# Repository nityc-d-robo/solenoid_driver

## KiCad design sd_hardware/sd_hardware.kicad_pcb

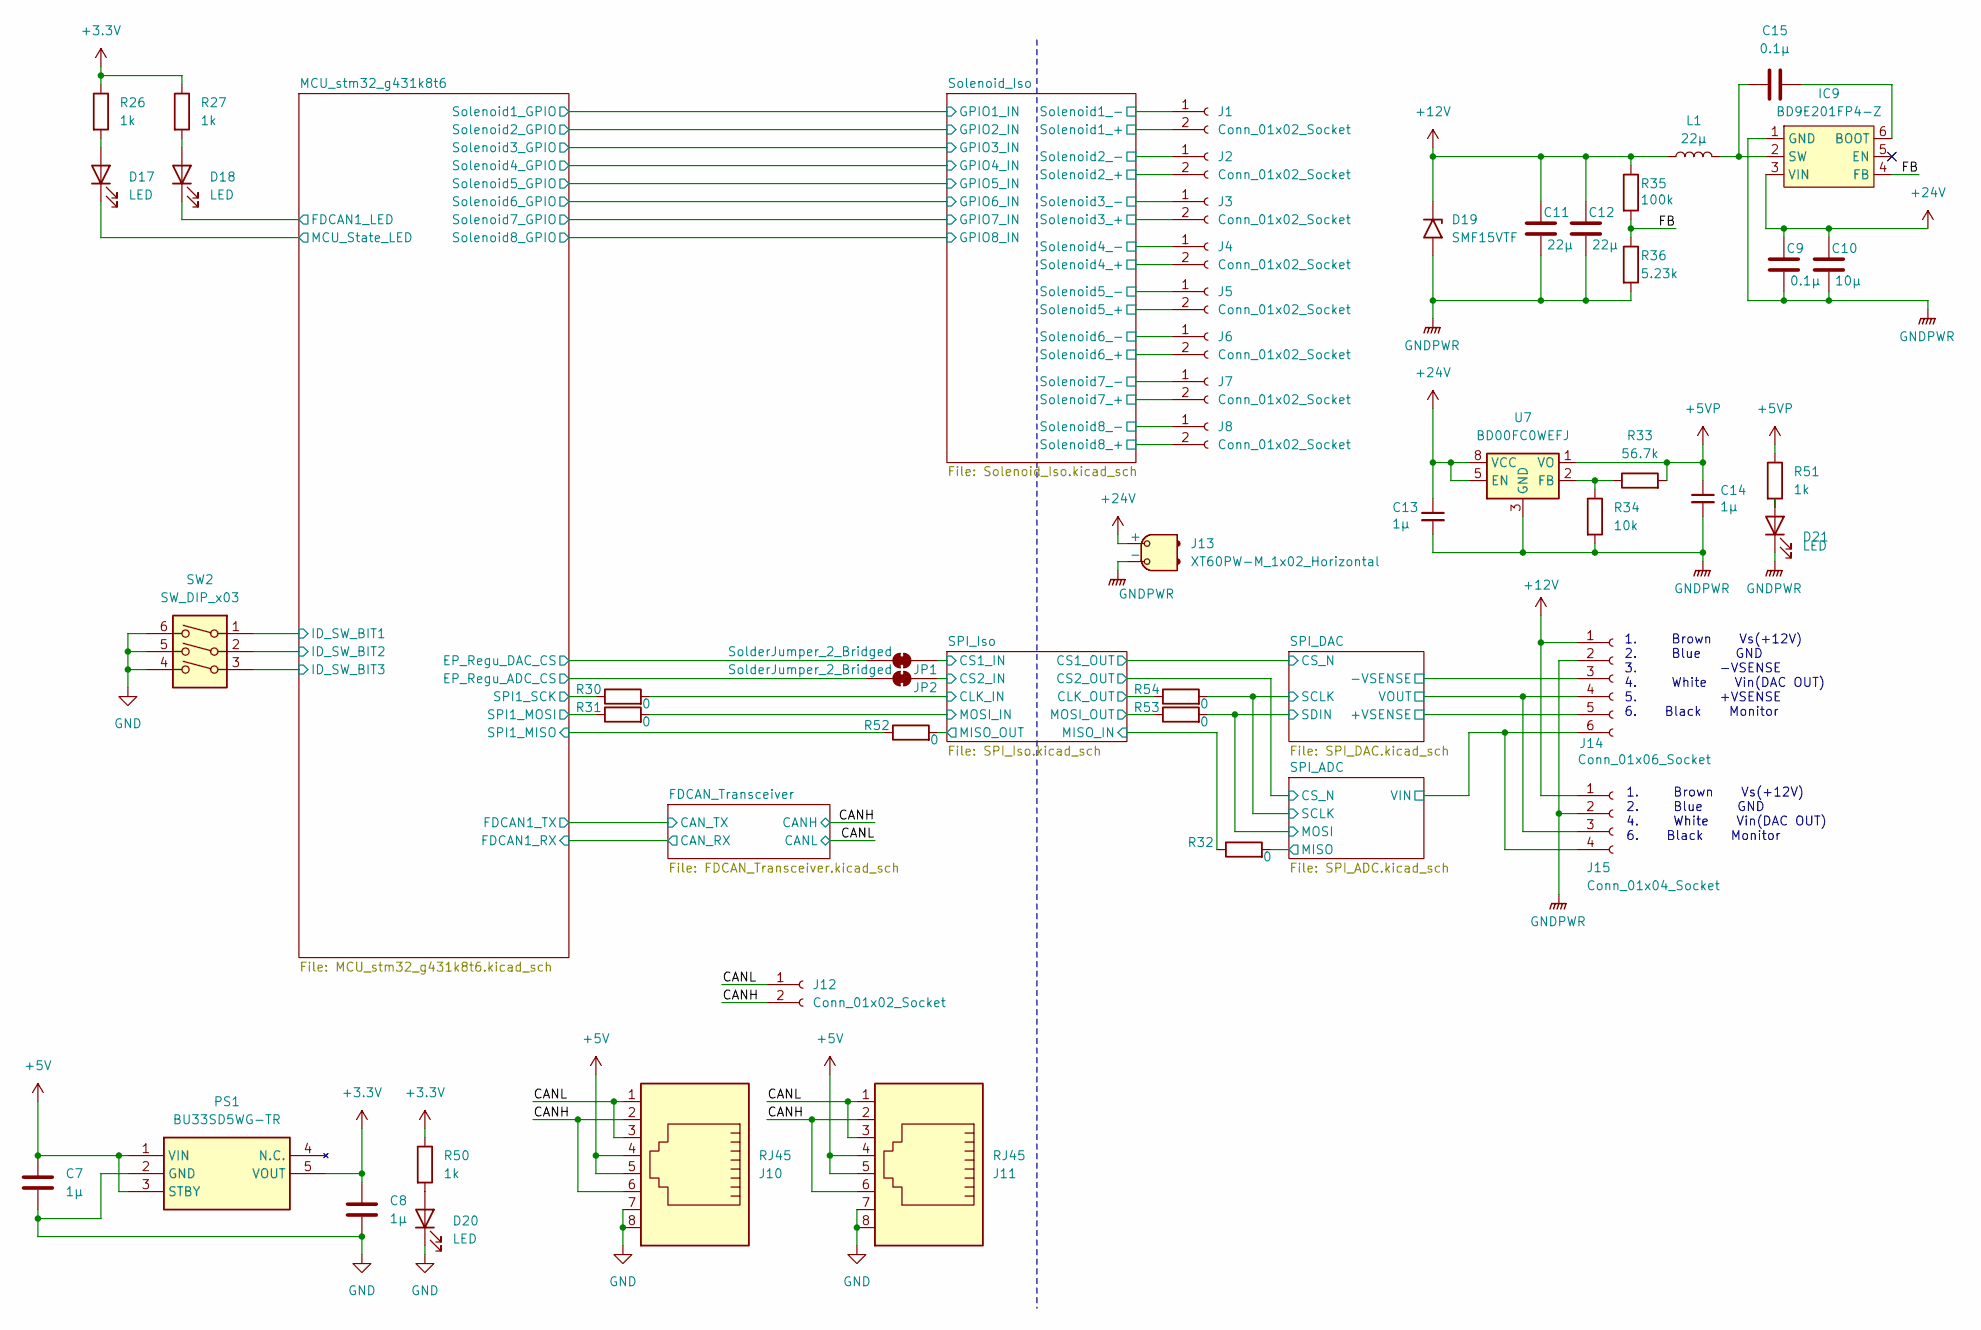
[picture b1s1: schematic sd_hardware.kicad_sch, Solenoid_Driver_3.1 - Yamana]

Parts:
C7, C8, C13, C14: 1μ; C_0603_1608Metric_Pad1.08x0.95mm_HandSolder
C9, C15: 0.1μ; C_0603_1608Metric_Pad1.08x0.95mm_HandSolder
C10: 10μ; C_0603_1608Metric_Pad1.08x0.95mm_HandSolder
C11, C12: 22μ; C_1210_3225Metric_Pad1.33x2.70mm_HandSolder
D17, D18, D20, D21: LED; LED_0603_1608Metric_Pad1.05x0.95mm_HandSolder
D19: SMF15VTF; D_SOD-123F
IC9: BD9E201FP4-Z; TSOT-23-6
J1, J2, J3, J4, J5, J6, J7, J8, J12: Conn_01x02_Socket; JST_XH_B2B-XH-A_1x02_P2.50mm_Vertical
J10, J11: RJ45; RJ45_Amphenol_54602-x08_Horizontal
J13: XT60PW-M_1x02_Horizontal; AMASS_XT60PW-M_1x02_P7.20mm_Horizontal
J14: Conn_01x06_Socket; JST_XH_B6B-XH-A_1x06_P2.50mm_Vertical
J15: Conn_01x04_Socket; JST_XH_B4B-XH-A_1x04_P2.50mm_Vertical
JP1, JP2: SolderJumper_2_Bridged; SolderJumper-2_P1.3mm_Bridged2Bar_RoundedPad1.0x1.5mm
L1: 22μ; RP1315BNP-220M
PS1: BU33SD5WG-TR; SOT95P280X125-5N; Mouser Part Number 755-BU33SD5WG-TR
R26, R27, R50, R51: 1k; R_0603_1608Metric_Pad0.98x0.95mm_HandSolder
R30, R31, R32, R52, R53, R54: 0; R_0603_1608Metric_Pad0.98x0.95mm_HandSolder
R33: 56.7k; R_0603_1608Metric_Pad0.98x0.95mm_HandSolder
R34: 10k; R_0603_1608Metric_Pad0.98x0.95mm_HandSolder
R35: 100k; R_0603_1608Metric_Pad0.98x0.95mm_HandSolder
R36: 5.23k; R_0603_1608Metric_Pad0.98x0.95mm_HandSolder
SW2: SW_DIP_x03; DS04-254-2-03BK-SMT
U7: BD00FC0WEFJ; HTSOP-8-1EP_3.9x4.9mm_P1.27mm_EP2.4x3.2mm

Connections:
+3.3V: C8.1, PS1.5 (VOUT), R26.1, R27.1, R50.1; also elsewhere on the board
+5V: C7.1, J10.4, J10.5, J11.4, J11.5, PS1.1 (VIN), PS1.3 (STBY); also elsewhere on the board
+5VP: C14.1, R33.2, R51.1, U7.1 (VO); also elsewhere on the board
+12V: C11.1, C12.1, D19.1 (A1), J1.2, J2.2, J3.2, J4.2, J5.2, J6.2, J7.2, J8.2, J14.1, J15.1, L1.1, R35.1; also elsewhere on the board
+24V: C9.1, C10.1, C13.1, IC9.3 (VIN), J13.2 (+), U7.5 (EN), U7.8 (VCC)
/CANH: J10.2, J10.6, J11.2, J11.6, J12.2; also elsewhere on the board
/CANL: J10.1, J10.3, J11.1, J11.3, J12.1; also elsewhere on the board
/FB: IC9.4 (FB), R35.2, R36.1
/MCU_stm32_g431k8t6/EP_Regu_ADC_CS: JP2.1 (A); also elsewhere on the board
/MCU_stm32_g431k8t6/EP_Regu_DAC_CS: JP1.1 (A); also elsewhere on the board
/MCU_stm32_g431k8t6/FDCAN1_LED: D18.1 (K); also elsewhere on the board
/MCU_stm32_g431k8t6/ID_SW_BIT1: SW2.1; also elsewhere on the board
/MCU_stm32_g431k8t6/ID_SW_BIT2: SW2.2; also elsewhere on the board
/MCU_stm32_g431k8t6/ID_SW_BIT3: SW2.3; also elsewhere on the board
/MCU_stm32_g431k8t6/MCU_State_LED: D17.1 (K); also elsewhere on the board
/MCU_stm32_g431k8t6/SPI1_MISO: R52.1; also elsewhere on the board
/MCU_stm32_g431k8t6/SPI1_MOSI: R31.1; also elsewhere on the board
/MCU_stm32_g431k8t6/SPI1_SCK: R30.1; also elsewhere on the board
/SPI_ADC/MISO: R32.2; also elsewhere on the board
/SPI_ADC/MOSI: R53.2; also elsewhere on the board
/SPI_ADC/SCLK: R54.2; also elsewhere on the board
/SPI_ADC/VIN: J14.6, J15.4; also elsewhere on the board
/SPI_DAC/+VSENSE: J14.5; also elsewhere on the board
/SPI_DAC/-VSENSE: J14.3; also elsewhere on the board
/SPI_DAC/VOUT: J14.4, J15.3; also elsewhere on the board
/SPI_Iso/CLK_IN: R30.2; also elsewhere on the board
/SPI_Iso/CLK_OUT: R54.1; also elsewhere on the board
/SPI_Iso/CS1_IN: JP1.2 (B); also elsewhere on the board
/SPI_Iso/CS2_IN: JP2.2 (B); also elsewhere on the board
/SPI_Iso/MISO_IN: R32.1; also elsewhere on the board
/SPI_Iso/MISO_OUT: R52.2; also elsewhere on the board
/SPI_Iso/MOSI_IN: R31.2; also elsewhere on the board
/SPI_Iso/MOSI_OUT: R53.1; also elsewhere on the board
/Solenoid_Iso/PhotoRelay1_Drain: J1.1; also elsewhere on the board
/Solenoid_Iso/PhotoRelay2_Drain: J2.1; also elsewhere on the board
/Solenoid_Iso/PhotoRelay3_Drain: J3.1; also elsewhere on the board
/Solenoid_Iso/PhotoRelay4_Drain: J4.1; also elsewhere on the board
/Solenoid_Iso/PhotoRelay5_Drain: J5.1; also elsewhere on the board
/Solenoid_Iso/PhotoRelay6_Drain: J6.1; also elsewhere on the board
/Solenoid_Iso/PhotoRelay7_Drain: J7.1; also elsewhere on the board
/Solenoid_Iso/PhotoRelay8_Drain: J8.1; also elsewhere on the board
GND: C7.2, C8.2, D20.1 (K), J10.7, J10.8, J11.7, J11.8, PS1.2 (GND), SW2.4, SW2.5, SW2.6; also elsewhere on the board
GNDPWR: C9.2, C10.2, C11.2, C12.2, C13.2, C14.2, D19.2 (A2), D21.1 (K), IC9.1 (GND), J13.1 (-), J14.2, J15.2, R34.2, R36.2, U7.3 (GND), U7.9 (GND); also elsewhere on the board
unnamed: D17.2 (A), R26.2
unnamed: D18.2 (A), R27.2
unnamed: D20.2 (A), R50.2
unnamed: D21.2 (A), R51.2
unnamed: C15.2, IC9.6 (BOOT)
unnamed: C15.1, IC9.2 (SW), L1.2
unnamed: R33.1, R34.1, U7.2 (FB)

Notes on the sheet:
1. Brown Vs(+12V) 2. Blue GND 3. -VSENSE 4. White Vin(DAC OUT) 5. +VSENSE 6. Black Monitor
1. Brown Vs(+12V) 2. Blue GND 4. White Vin(DAC OUT) 6. Black Monitor

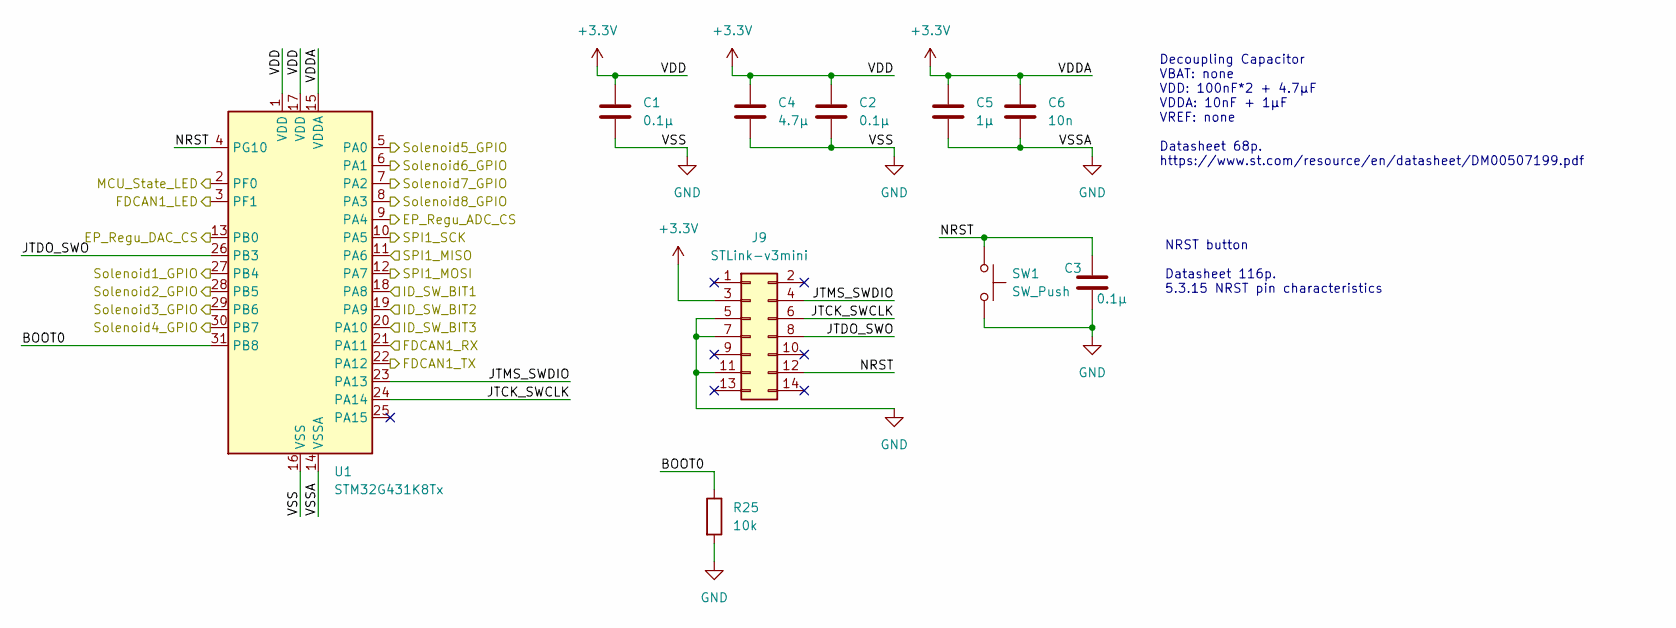
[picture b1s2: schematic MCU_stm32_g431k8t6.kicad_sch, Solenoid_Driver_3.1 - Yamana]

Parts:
C1, C2, C3: 0.1μ; C_0603_1608Metric_Pad1.08x0.95mm_HandSolder
C4: 4.7μ; C_0603_1608Metric_Pad1.08x0.95mm_HandSolder
C5: 1μ; C_0603_1608Metric_Pad1.08x0.95mm_HandSolder
C6: 10n; C_0603_1608Metric_Pad1.08x0.95mm_HandSolder
J9: STLink-v3mini; CONN14_3220-14_CNC
R25: 10k; R_0603_1608Metric_Pad0.98x0.95mm_HandSolder
SW1: SW_Push; TVAF06-A020B-R
U1: STM32G431K8Tx; LQFP-32_7x7mm_P0.8mm

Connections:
+3.3V: C1.1, C2.1, C4.1, C5.1, C6.1, J9.3, U1.1 (VDD), U1.15 (VDDA), U1.17 (VDD); also elsewhere on the board
/FDCAN_Transceiver/CAN_RX: U1.21 (PA11); also elsewhere on the board
/FDCAN_Transceiver/CAN_TX: U1.22 (PA12); also elsewhere on the board
/MCU_stm32_g431k8t6/BOOT0: R25.1, U1.31 (PB8)
/MCU_stm32_g431k8t6/EP_Regu_ADC_CS: U1.9 (PA4); also elsewhere on the board
/MCU_stm32_g431k8t6/EP_Regu_DAC_CS: U1.13 (PB0); also elsewhere on the board
/MCU_stm32_g431k8t6/FDCAN1_LED: U1.3 (PF1); also elsewhere on the board
/MCU_stm32_g431k8t6/ID_SW_BIT1: U1.18 (PA8); also elsewhere on the board
/MCU_stm32_g431k8t6/ID_SW_BIT2: U1.19 (PA9); also elsewhere on the board
/MCU_stm32_g431k8t6/ID_SW_BIT3: U1.20 (PA10); also elsewhere on the board
/MCU_stm32_g431k8t6/JTCK_SWCLK: J9.6, U1.24 (PA14)
/MCU_stm32_g431k8t6/JTDO_SWO: J9.8, U1.26 (PB3)
/MCU_stm32_g431k8t6/JTMS_SWDIO: J9.4, U1.23 (PA13)
/MCU_stm32_g431k8t6/MCU_State_LED: U1.2 (PF0); also elsewhere on the board
/MCU_stm32_g431k8t6/NRST: C3.1, J9.12, SW1.1, U1.4 (PG10)
/MCU_stm32_g431k8t6/SPI1_MISO: U1.11 (PA6); also elsewhere on the board
/MCU_stm32_g431k8t6/SPI1_MOSI: U1.12 (PA7); also elsewhere on the board
/MCU_stm32_g431k8t6/SPI1_SCK: U1.10 (PA5); also elsewhere on the board
/MCU_stm32_g431k8t6/Solenoid1_GPIO: U1.27 (PB4); also elsewhere on the board
/MCU_stm32_g431k8t6/Solenoid2_GPIO: U1.28 (PB5); also elsewhere on the board
/MCU_stm32_g431k8t6/Solenoid3_GPIO: U1.29 (PB6); also elsewhere on the board
/MCU_stm32_g431k8t6/Solenoid4_GPIO: U1.30 (PB7); also elsewhere on the board
/MCU_stm32_g431k8t6/Solenoid5_GPIO: U1.5 (PA0); also elsewhere on the board
/MCU_stm32_g431k8t6/Solenoid6_GPIO: U1.6 (PA1); also elsewhere on the board
/MCU_stm32_g431k8t6/Solenoid7_GPIO: U1.7 (PA2); also elsewhere on the board
/MCU_stm32_g431k8t6/Solenoid8_GPIO: U1.8 (PA3); also elsewhere on the board
GND: C1.2, C2.2, C3.2, C4.2, C5.2, C6.2, J9.5, J9.7, J9.11, R25.2, SW1.2, U1.14 (VSSA), U1.16 (VSS), U1.32 (VSS); also elsewhere on the board

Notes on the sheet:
Decoupling Capacitor VBAT: none VDD: 100nF*2 + 4.7μF VDDA: 10nF + 1μF VREF: none Datasheet 68p. https://www.st.com/resource/en/datasheet/DM00507199.pdf
NRST button Datasheet 116p. 5.3.15 NRST pin characteristics

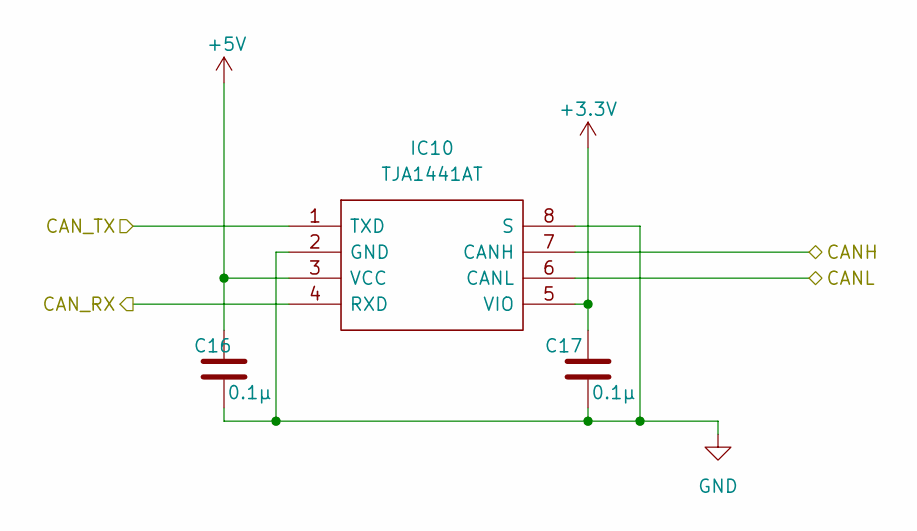
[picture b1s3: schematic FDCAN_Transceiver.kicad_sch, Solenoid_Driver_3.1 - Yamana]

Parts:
C16, C17: 0.1μ; C_0603_1608Metric_Pad1.08x0.95mm_HandSolder
IC10: TJA1441AT; SOIC127P600X175-8N; Manufacturer_Part_Number TJA1441AT

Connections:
+3.3V: C17.1, IC10.5 (VIO); also elsewhere on the board
+5V: C16.1, IC10.3 (VCC); also elsewhere on the board
/CANH: IC10.7 (CANH); also elsewhere on the board
/CANL: IC10.6 (CANL); also elsewhere on the board
/FDCAN_Transceiver/CAN_RX: IC10.4 (RXD); also elsewhere on the board
/FDCAN_Transceiver/CAN_TX: IC10.1 (TXD); also elsewhere on the board
GND: C16.2, C17.2, IC10.2 (GND), IC10.8 (S); also elsewhere on the board

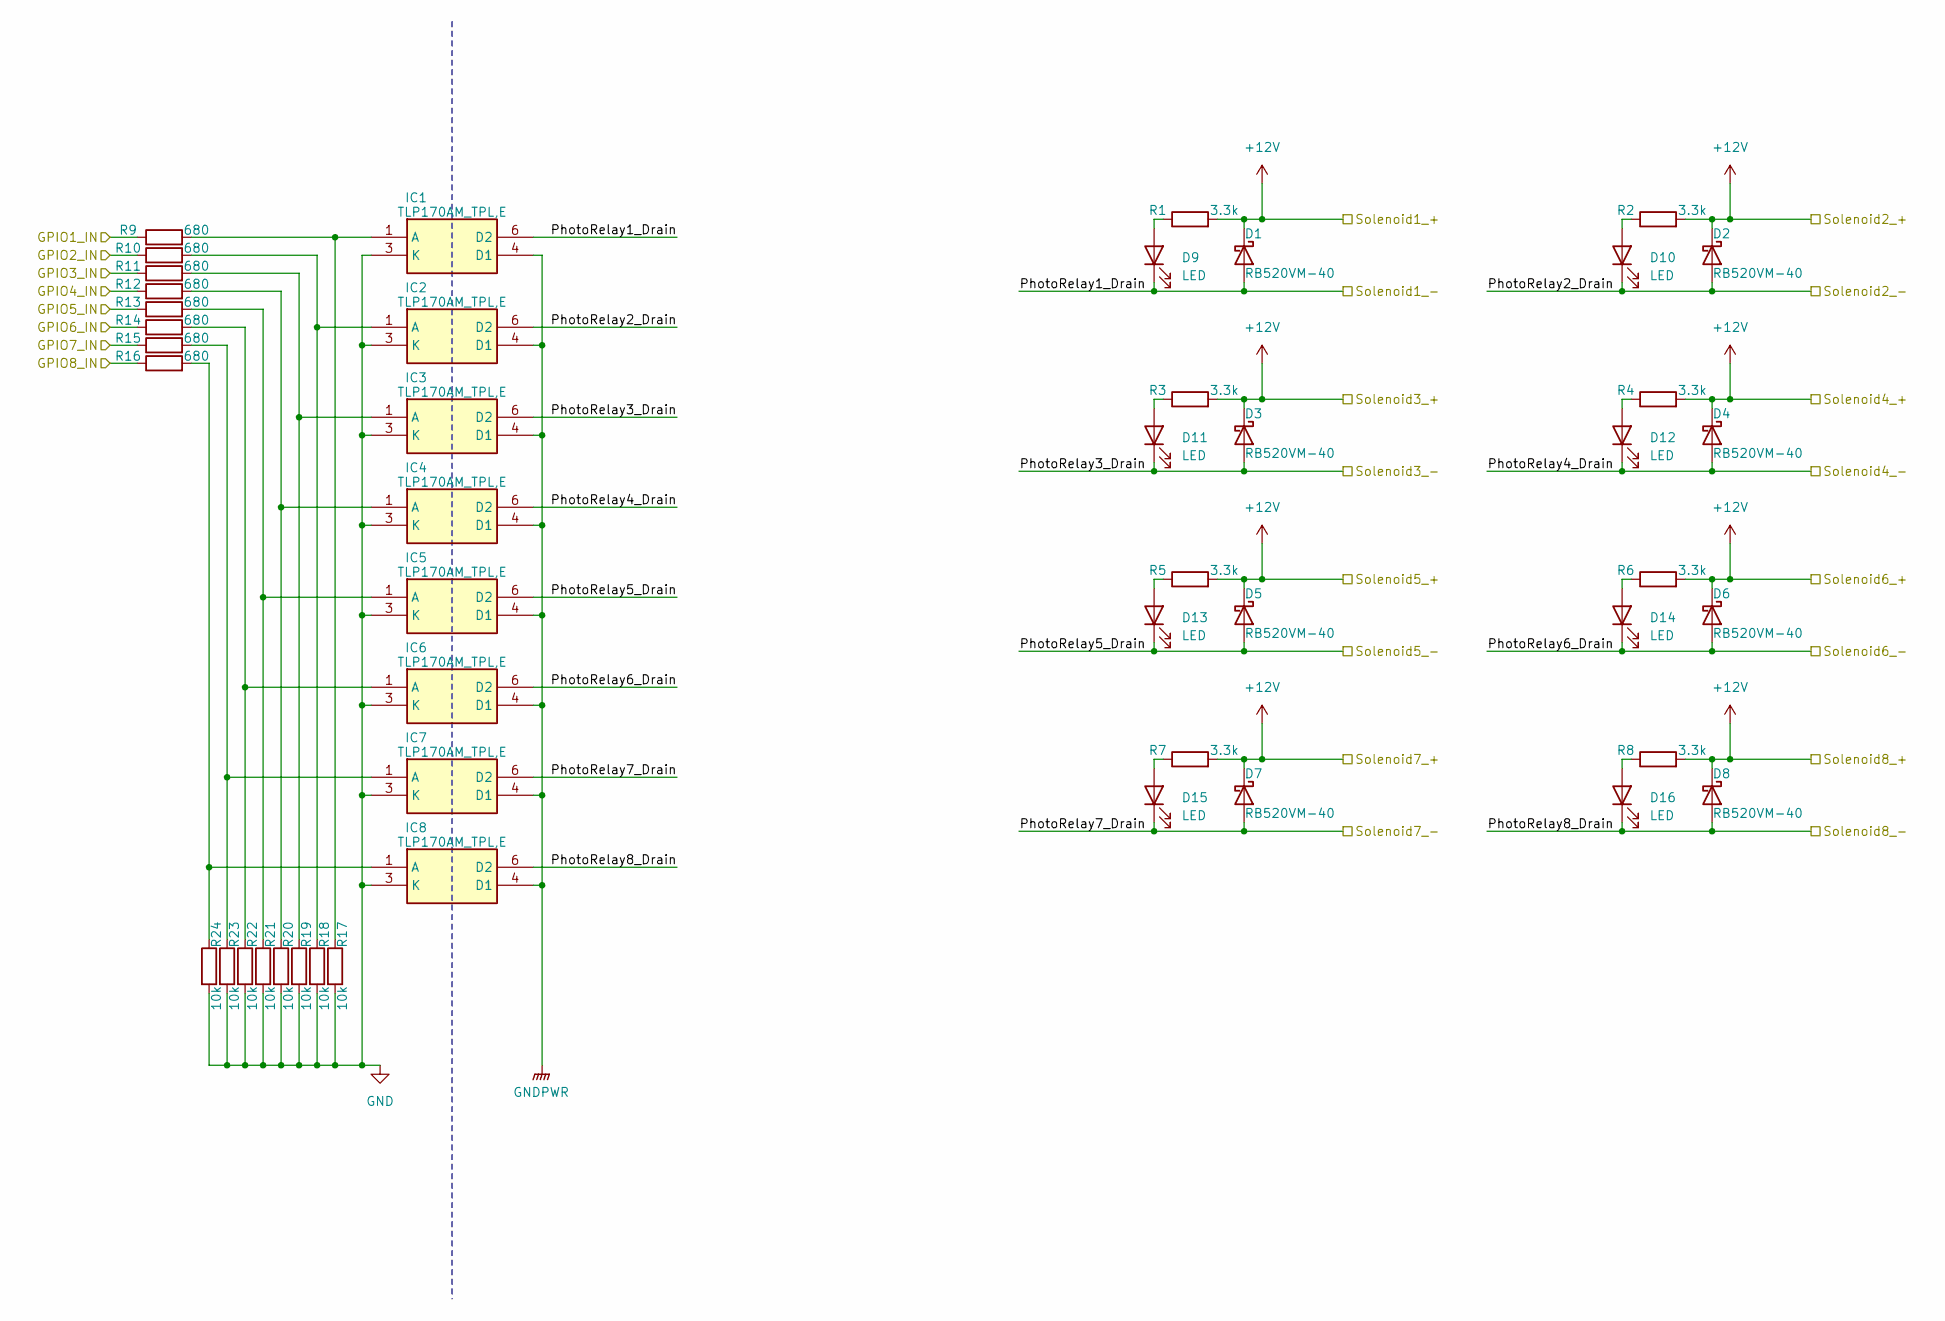
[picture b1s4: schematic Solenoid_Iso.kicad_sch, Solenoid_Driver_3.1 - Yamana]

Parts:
D1, D2, D3, D4, D5, D6, D7, D8: RB520VM-40; D_SOD-323_HandSoldering
D9, D10, D11, D12, D13, D14, D15, D16: LED; LED_0603_1608Metric_Pad1.05x0.95mm_HandSolder
IC1, IC2, IC3, IC4, IC5, IC6, IC7, IC8: TLP170AM_TPL,E; TLP170AMTPLE; Mouser Part Number 757-TLP170AM(TPL,E
R1, R2, R3, R4, R5, R6, R7, R8: 3.3k; R_0603_1608Metric_Pad0.98x0.95mm_HandSolder
R9, R10, R11, R12, R13, R14, R15, R16: 680; R_0603_1608Metric_Pad0.98x0.95mm_HandSolder
R17, R18, R19, R20, R21, R22, R23, R24: 10k; R_0603_1608Metric_Pad0.98x0.95mm_HandSolder

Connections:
+12V: D1.1 (K), D2.1 (K), D3.1 (K), D4.1 (K), D5.1 (K), D6.1 (K), D7.1 (K), D8.1 (K), R1.2, R2.2, R3.2, R4.2, R5.2, R6.2, R7.2, R8.2; also elsewhere on the board
/MCU_stm32_g431k8t6/Solenoid1_GPIO: R9.1; also elsewhere on the board
/MCU_stm32_g431k8t6/Solenoid2_GPIO: R10.1; also elsewhere on the board
/MCU_stm32_g431k8t6/Solenoid3_GPIO: R11.1; also elsewhere on the board
/MCU_stm32_g431k8t6/Solenoid4_GPIO: R12.1; also elsewhere on the board
/MCU_stm32_g431k8t6/Solenoid5_GPIO: R13.1; also elsewhere on the board
/MCU_stm32_g431k8t6/Solenoid6_GPIO: R14.1; also elsewhere on the board
/MCU_stm32_g431k8t6/Solenoid7_GPIO: R15.1; also elsewhere on the board
/MCU_stm32_g431k8t6/Solenoid8_GPIO: R16.1; also elsewhere on the board
/Solenoid_Iso/PhotoRelay1_Drain: D1.2 (A), D9.1 (K), IC1.6 (D2); also elsewhere on the board
/Solenoid_Iso/PhotoRelay2_Drain: D2.2 (A), D10.1 (K), IC2.6 (D2); also elsewhere on the board
/Solenoid_Iso/PhotoRelay3_Drain: D3.2 (A), D11.1 (K), IC3.6 (D2); also elsewhere on the board
/Solenoid_Iso/PhotoRelay4_Drain: D4.2 (A), D12.1 (K), IC4.6 (D2); also elsewhere on the board
/Solenoid_Iso/PhotoRelay5_Drain: D5.2 (A), D13.1 (K), IC5.6 (D2); also elsewhere on the board
/Solenoid_Iso/PhotoRelay6_Drain: D6.2 (A), D14.1 (K), IC6.6 (D2); also elsewhere on the board
/Solenoid_Iso/PhotoRelay7_Drain: D7.2 (A), D15.1 (K), IC7.6 (D2); also elsewhere on the board
/Solenoid_Iso/PhotoRelay8_Drain: D8.2 (A), D16.1 (K), IC8.6 (D2); also elsewhere on the board
GND: IC1.3 (K), IC2.3 (K), IC3.3 (K), IC4.3 (K), IC5.3 (K), IC6.3 (K), IC7.3 (K), IC8.3 (K), R17.2, R18.2, R19.2, R20.2, R21.2, R22.2, R23.2, R24.2; also elsewhere on the board
GNDPWR: IC1.4 (D1), IC2.4 (D1), IC3.4 (D1), IC4.4 (D1), IC5.4 (D1), IC6.4 (D1), IC7.4 (D1), IC8.4 (D1); also elsewhere on the board
unnamed: D9.2 (A), R1.1
unnamed: D10.2 (A), R2.1
unnamed: D11.2 (A), R3.1
unnamed: D12.2 (A), R4.1
unnamed: D13.2 (A), R5.1
unnamed: D14.2 (A), R6.1
unnamed: D15.2 (A), R7.1
unnamed: D16.2 (A), R8.1
unnamed: IC1.1 (A), R9.2, R17.1
unnamed: IC2.1 (A), R10.2, R18.1
unnamed: IC3.1 (A), R11.2, R19.1
unnamed: IC4.1 (A), R12.2, R20.1
unnamed: IC5.1 (A), R13.2, R21.1
unnamed: IC6.1 (A), R14.2, R22.1
unnamed: IC7.1 (A), R15.2, R23.1
unnamed: IC8.1 (A), R16.2, R24.1

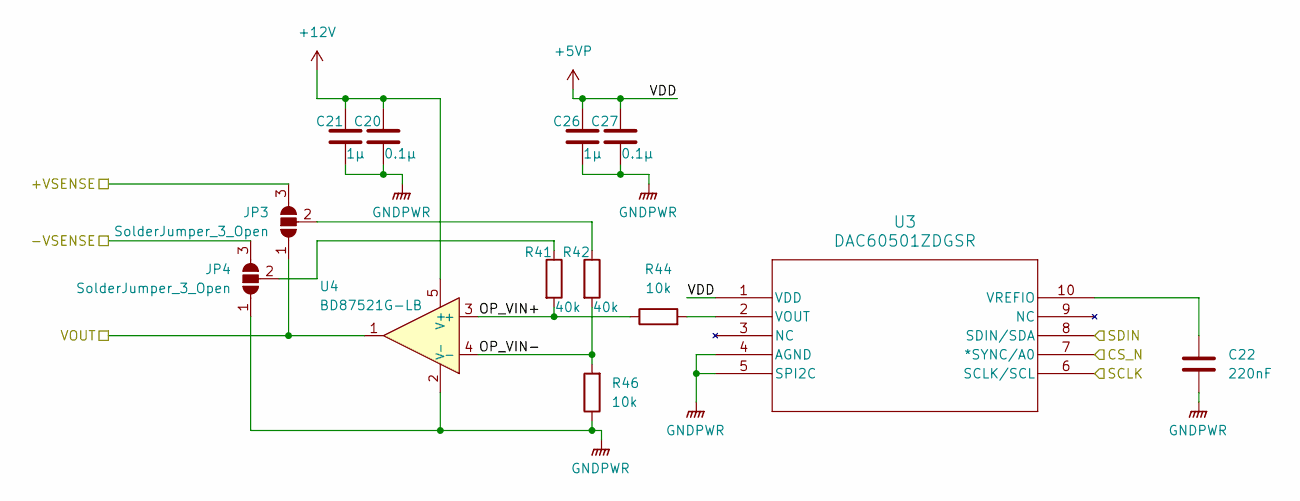
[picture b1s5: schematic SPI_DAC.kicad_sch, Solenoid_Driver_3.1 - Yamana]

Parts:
C20, C27: 0.1μ; C_0603_1608Metric_Pad1.08x0.95mm_HandSolder
C21, C26: 1μ; C_0603_1608Metric_Pad1.08x0.95mm_HandSolder
C22: 220nF; C_0603_1608Metric_Pad1.08x0.95mm_HandSolder
JP3, JP4: SolderJumper_3_Open; SolderJumper-3_P1.3mm_Open_RoundedPad1.0x1.5mm_NumberLabels
R41, R42: 40k; R_0603_1608Metric_Pad0.98x0.95mm_HandSolder
R44, R46: 10k; R_0603_1608Metric_Pad0.98x0.95mm_HandSolder
U3: DAC60501ZDGSR; DGS10_TEX
U4: BD87521G-LB; SOT95P280X125-5N

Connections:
+5VP: C26.1, C27.1, U3.1 (VDD); also elsewhere on the board
+12V: C20.1, C21.1, U4.5 (V+); also elsewhere on the board
/SPI_ADC/MOSI: U3.8 (SDIN/SDA); also elsewhere on the board
/SPI_ADC/SCLK: U3.6 (SCLK/SCL); also elsewhere on the board
/SPI_DAC/+VSENSE: JP3.3 (B); also elsewhere on the board
/SPI_DAC/-VSENSE: JP4.3 (B); also elsewhere on the board
/SPI_DAC/CS_N: U3.7 (*SYNC/A0); also elsewhere on the board
/SPI_DAC/OP_VIN+: R41.2, R44.1, U4.3 (+)
/SPI_DAC/OP_VIN-: R42.2, R46.2, U4.4 (-)
/SPI_DAC/VOUT: JP3.1 (A), U4.1; also elsewhere on the board
GNDPWR: C20.2, C21.2, C22.2, C26.2, C27.2, JP4.1 (A), R46.1, U3.4 (AGND), U3.5 (SPI2C), U4.2 (V-); also elsewhere on the board
unnamed: JP3.2 (C), R42.1
unnamed: JP4.2 (C), R41.1
unnamed: R44.2, U3.2 (VOUT)
unnamed: C22.1, U3.10 (VREFIO)

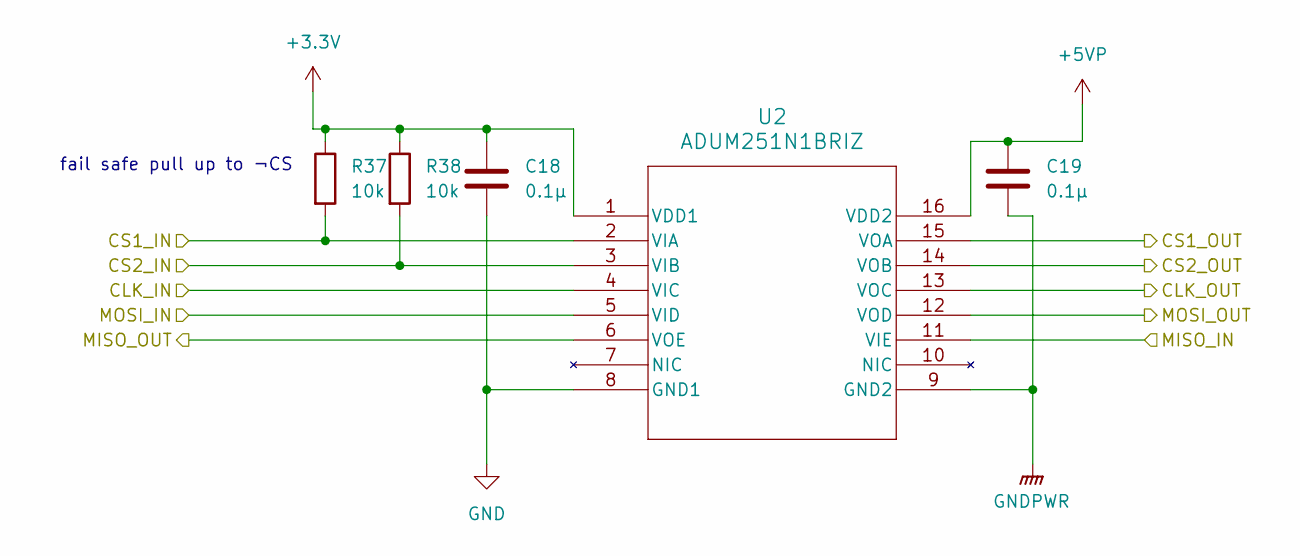
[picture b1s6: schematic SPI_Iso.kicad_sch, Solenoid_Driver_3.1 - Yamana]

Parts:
C18, C19: 0.1μ; C_0603_1608Metric_Pad1.08x0.95mm_HandSolder
R37, R38: 10k; R_0603_1608Metric_Pad0.98x0.95mm_HandSolder
U2: ADUM251N1BRIZ; ADUM251N1BRIZ_ADI

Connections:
+3.3V: C18.1, R37.1, R38.1, U2.1 (VDD1); also elsewhere on the board
+5VP: C19.1, U2.16 (VDD2); also elsewhere on the board
/SPI_ADC/CS_N: U2.14 (VOB); also elsewhere on the board
/SPI_DAC/CS_N: U2.15 (VOA); also elsewhere on the board
/SPI_Iso/CLK_IN: U2.4 (VIC); also elsewhere on the board
/SPI_Iso/CLK_OUT: U2.13 (VOC); also elsewhere on the board
/SPI_Iso/CS1_IN: R37.2, U2.2 (VIA); also elsewhere on the board
/SPI_Iso/CS2_IN: R38.2, U2.3 (VIB); also elsewhere on the board
/SPI_Iso/MISO_IN: U2.11 (VIE); also elsewhere on the board
/SPI_Iso/MISO_OUT: U2.6 (VOE); also elsewhere on the board
/SPI_Iso/MOSI_IN: U2.5 (VID); also elsewhere on the board
/SPI_Iso/MOSI_OUT: U2.12 (VOD); also elsewhere on the board
GND: C18.2, U2.8 (GND1); also elsewhere on the board
GNDPWR: C19.2, U2.9 (GND2); also elsewhere on the board

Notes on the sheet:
fail safe pull up to ¬CS

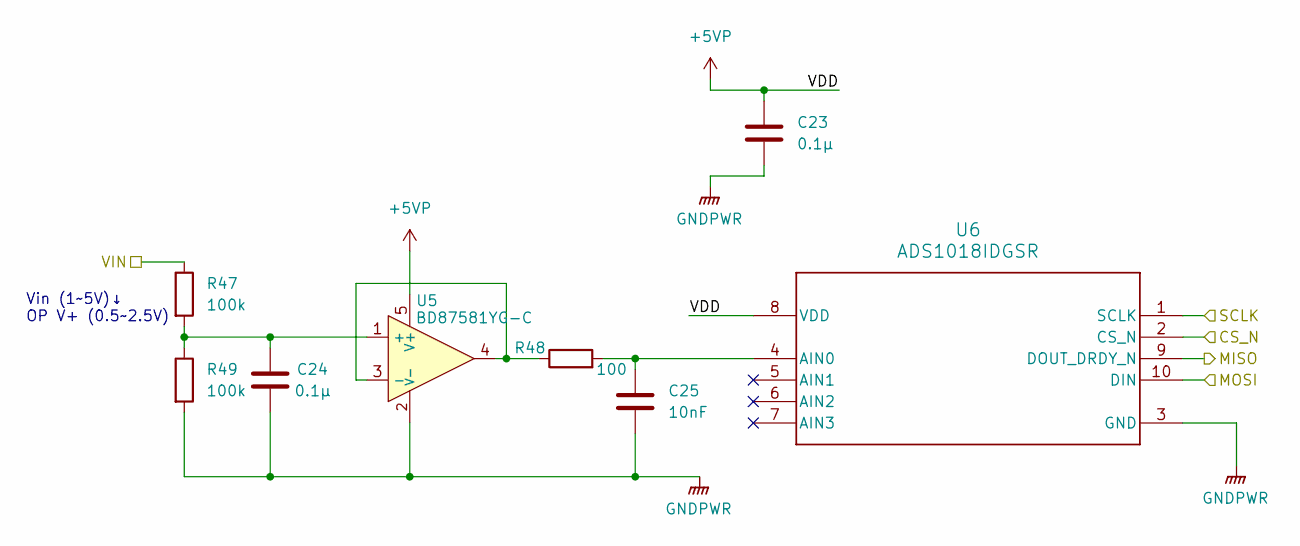
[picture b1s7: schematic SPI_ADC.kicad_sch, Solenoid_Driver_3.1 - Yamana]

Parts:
C23, C24: 0.1μ; C_0603_1608Metric_Pad1.08x0.95mm_HandSolder
C25: 10nF; C_0603_1608Metric_Pad1.08x0.95mm_HandSolder
R47, R49: 100k; R_0603_1608Metric_Pad0.98x0.95mm_HandSolder
R48: 100; R_0603_1608Metric_Pad0.98x0.95mm_HandSolder
U5: BD87581YG-C; SOT95P280X125-5N
U6: ADS1018IDGSR; DGS10_TEX

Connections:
+5VP: C23.1, U5.5 (V+), U6.8 (VDD); also elsewhere on the board
/SPI_ADC/CS_N: U6.2 (CS_N); also elsewhere on the board
/SPI_ADC/MISO: U6.9 (DOUT_DRDY_N); also elsewhere on the board
/SPI_ADC/MOSI: U6.10 (DIN); also elsewhere on the board
/SPI_ADC/SCLK: U6.1 (SCLK); also elsewhere on the board
/SPI_ADC/VIN: R47.1; also elsewhere on the board
GNDPWR: C23.2, C24.2, C25.2, R49.2, U5.2 (V-), U6.3 (GND); also elsewhere on the board
unnamed: C24.1, R47.2, R49.1, U5.1 (+)
unnamed: R48.1, U5.3 (-), U5.4
unnamed: C25.1, R48.2, U6.4 (AIN0)

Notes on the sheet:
Vin (1~5V)↓ OP V+ (0.5~2.5V)

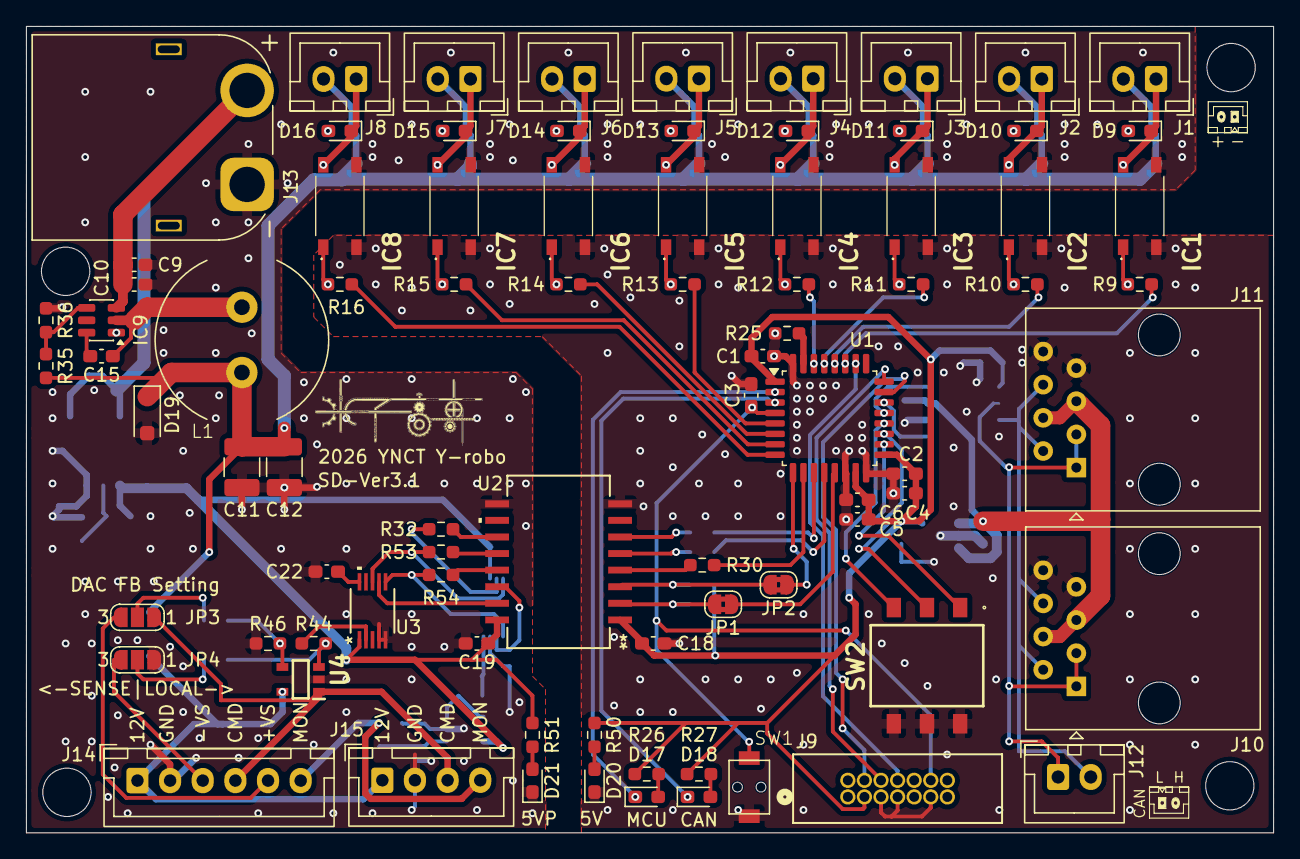
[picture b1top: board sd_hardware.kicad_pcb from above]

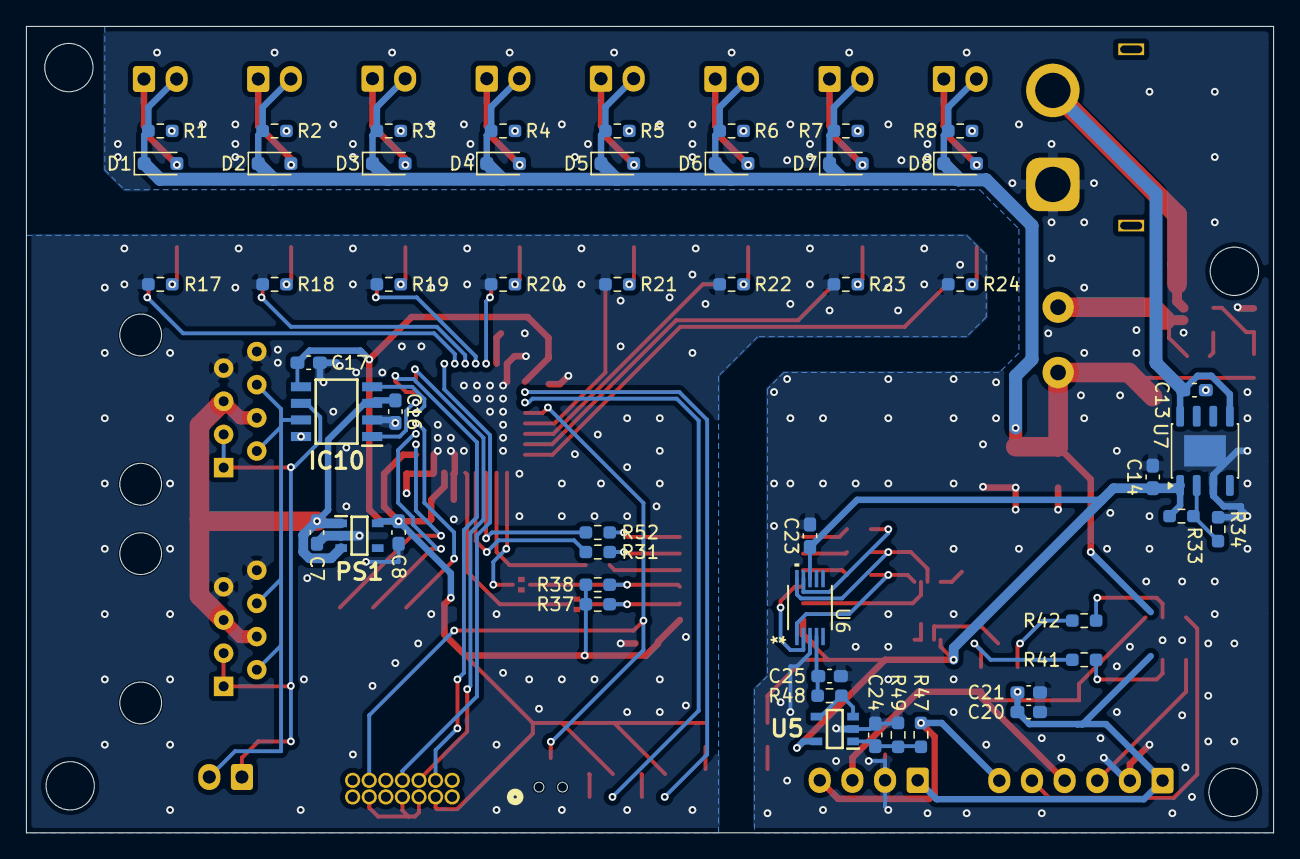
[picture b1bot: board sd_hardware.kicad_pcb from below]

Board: 2 copper layers, 95.5 x 61.8 mm, 134 parts (51 on the bottom side), 92 nets.

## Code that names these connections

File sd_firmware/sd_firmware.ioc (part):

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Mcu.Name=STM32G431K(6-8-B)Tx
Mcu.Package=LQFP32
Mcu.UserName=STM32G431K8Tx
PA0.GPIOParameters=GPIO_Label
PA0.GPIO_Label=Solenoid5_GPIO
PA0.Signal=GPIO_Output
PA1.GPIOParameters=GPIO_Label
PA1.GPIO_Label=Solenoid6_GPIO
PA1.Signal=GPIO_Output
PA10.GPIOParameters=GPIO_Label
PA10.GPIO_Label=ID_SW_BIT3
PA10.Signal=GPIO_Input
PA11.Mode=FDCAN_Activate
PA11.Signal=FDCAN1_RX
PA12.Mode=FDCAN_Activate
PA12.Signal=FDCAN1_TX
PA13.Mode=Trace_Asynchronous_SW
PA13.Signal=SYS_JTMS-SWDIO
PA14.Mode=Trace_Asynchronous_SW
PA14.Signal=SYS_JTCK-SWCLK
PA2.GPIOParameters=GPIO_Label
PA2.GPIO_Label=Solenoid7_GPIO
PA2.Signal=GPIO_Output
PA3.GPIOParameters=GPIO_Label
PA3.GPIO_Label=Solenoid8_GPIO
PA3.Signal=GPIO_Output
PA4.GPIOParameters=PinState,GPIO_Label
PA4.GPIO_Label=ADC_CS
PA4.PinState=GPIO_PIN_SET
PA4.Signal=GPIO_Output
PA5.Mode=Full_Duplex_Master
PA5.Signal=SPI1_SCK
PA6.Mode=Full_Duplex_Master
PA6.Signal=SPI1_MISO
PA7.Mode=Full_Duplex_Master
PA7.Signal=SPI1_MOSI
PA8.GPIOParameters=GPIO_Label
PA8.GPIO_Label=ID_SW_BIT1
PA8.Signal=GPIO_Input
PA9.GPIOParameters=GPIO_Label
PA9.GPIO_Label=ID_SW_BIT2
PA9.Signal=GPIO_Input
PB0.GPIOParameters=PinState,GPIO_Label
PB0.GPIO_Label=DAC_CS
PB0.PinState=GPIO_PIN_SET
PB0.Signal=GPIO_Output
PB3.Mode=Trace_Asynchronous_SW
PB3.Signal=SYS_JTDO-SWO
PB4.GPIOParameters=GPIO_Label
PB4.GPIO_Label=Solenoid1_GPIO
PB4.Signal=GPIO_Output
PB5.GPIOParameters=GPIO_Label
PB5.GPIO_Label=Solenoid2_GPIO
PB5.Signal=GPIO_Output
PB6.GPIOParameters=GPIO_Label
PB6.GPIO_Label=Solenoid3_GPIO
PB6.Signal=GPIO_Output
PB7.GPIOParameters=GPIO_Label
PB7.GPIO_Label=Solenoid4_GPIO
PB7.Signal=GPIO_Output
PF0-OSC_IN.GPIOParameters=GPIO_Label
PF0-OSC_IN.GPIO_Label=MCU_State_LED
PF0-OSC_IN.Signal=GPIO_Output
PF1-OSC_OUT.GPIOParameters=GPIO_Label
PF1-OSC_OUT.GPIO_Label=FDCAN1_LED
PF1-OSC_OUT.Signal=GPIO_Output
RCC.HSE_VALUE=8000000
RCC.SYSCLKFreq_VALUE=24000000
RCC.SYSCLKSource=RCC_SYSCLKSOURCE_PLLCLK
board=custom
